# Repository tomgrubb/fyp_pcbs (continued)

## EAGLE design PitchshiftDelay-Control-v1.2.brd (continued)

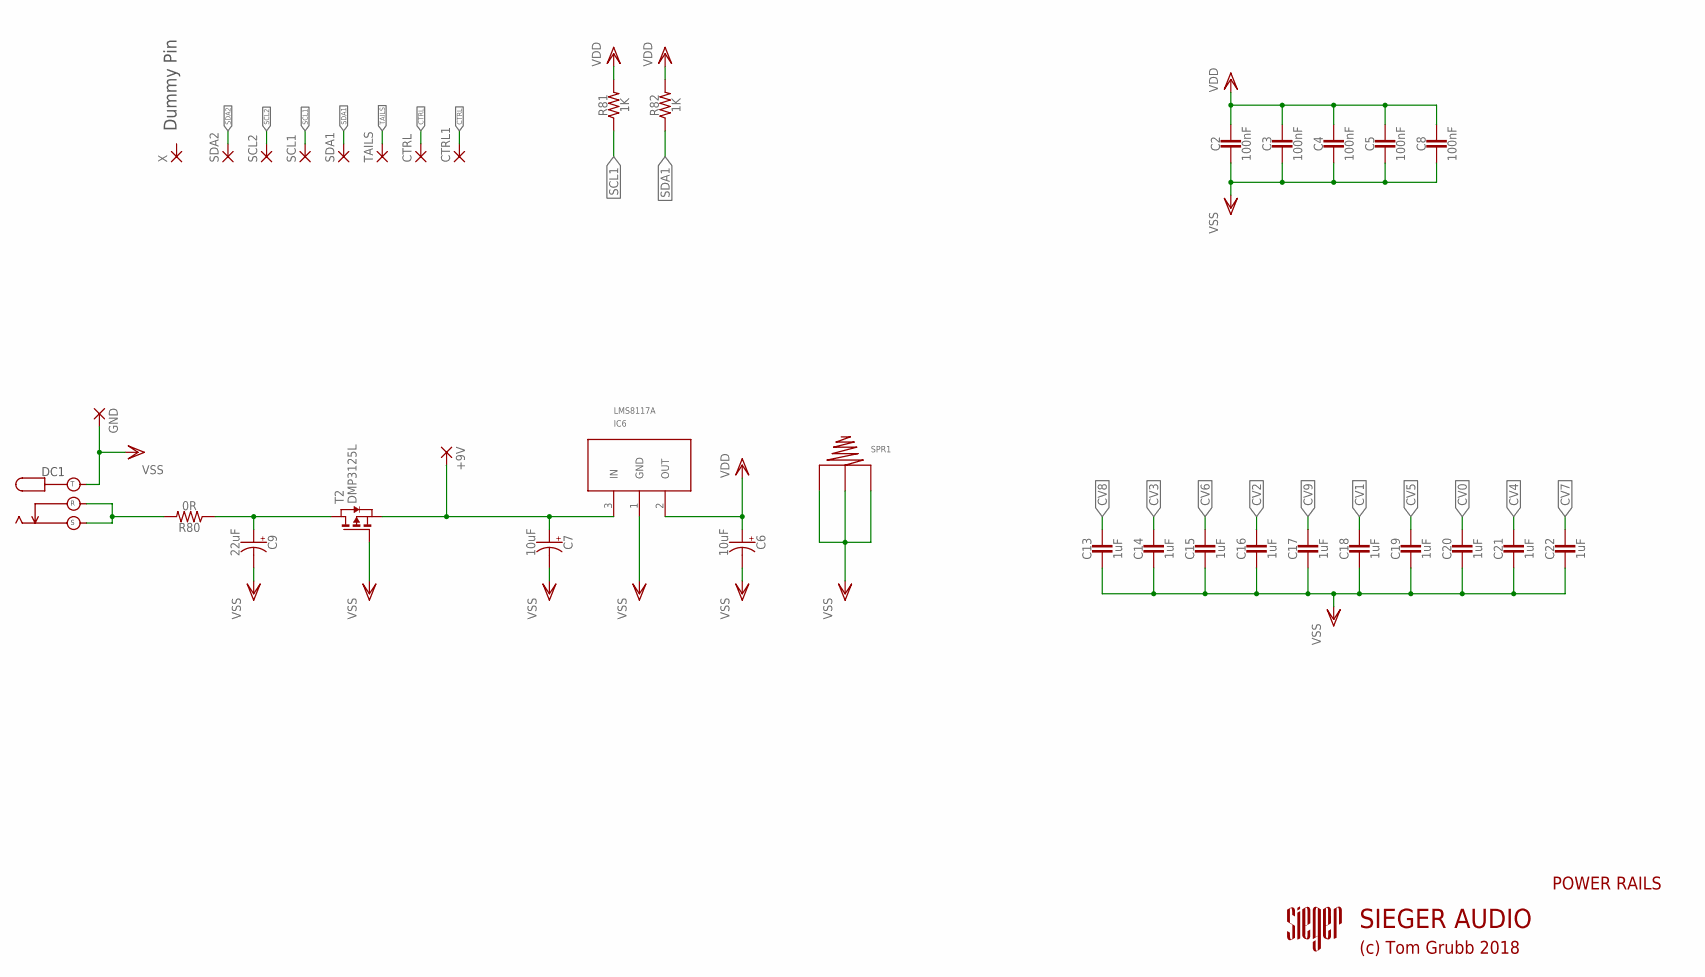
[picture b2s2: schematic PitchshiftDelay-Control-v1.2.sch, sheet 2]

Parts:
+9V: 2,15/1,0
C2, C3, C4, C5, C8: 100nF; 050X030_025
C6, C7: 10uF; 050_020_1
C9: 22uF; 050_020_1
C13, C14, C15, C16, C17, C18, C19, C20, C21, C22: 1uF; 050X030_025
CTRL, CTRL1: 2,15/1,0
DC1: DC_KOBICONN
GND: 2,15/1,0
IC6: LMS8117A; SOT223
R80: 0R; RESISTOR_C0805
R81, R82: 1K; RESISTOR_C0805
SCL1, SCL2: 2,15/1,0
SDA1, SDA2: 2,15/1,0
SPR1: 534-628; 'A'SIZE-PC-SPRING
T2: DMP3125L; SOT-23
TAILS: 2,15/1,0
X: 2,15/1,0

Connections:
9V: +9V.1, C7.+, IC6.3 (IN), T2.2 (S)
CTRL: CTRL.1, CTRL1.1; also elsewhere on the board
CV0: C20.1; also elsewhere on the board
CV1: C18.1; also elsewhere on the board
CV2: C16.1; also elsewhere on the board
CV3: C14.1; also elsewhere on the board
CV4: C21.1; also elsewhere on the board
CV5: C19.1; also elsewhere on the board
CV6: C15.1; also elsewhere on the board
CV7: C22.1; also elsewhere on the board
CV8: C13.1; also elsewhere on the board
CV9: C17.1; also elsewhere on the board
SCL1: R81.1, SCL1.1; also elsewhere on the board
SCL2: SCL2.1; also elsewhere on the board
SDA1: R82.1, SDA1.1; also elsewhere on the board
SDA2: SDA2.1; also elsewhere on the board
TAILS: TAILS.1; also elsewhere on the board
VDD: C2.1, C3.1, C4.1, C5.1, C6.+, C8.1, IC6.2 (OUT), R81.2, R82.2; also elsewhere on the board
VIN: DC1.R, DC1.S, R80.2
VINF: C9.+, R80.1, T2.1 (D)
VSS: C2.2, C3.2, C4.2, C5.2, C6.-, C7.-, C8.2, C9.-, C13.2, C14.2, C15.2, C16.2, C17.2, C18.2, C19.2, C20.2, C21.2, C22.2, DC1.T, GND.1, IC6.1 (GND), SPR1.P$1, SPR1.P$2, SPR1.P$3, T2.3 (G); also elsewhere on the board

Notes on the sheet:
POWER RAILS
Dummy Pin
(c) Tom Grubb 2018
SIEGER AUDIO

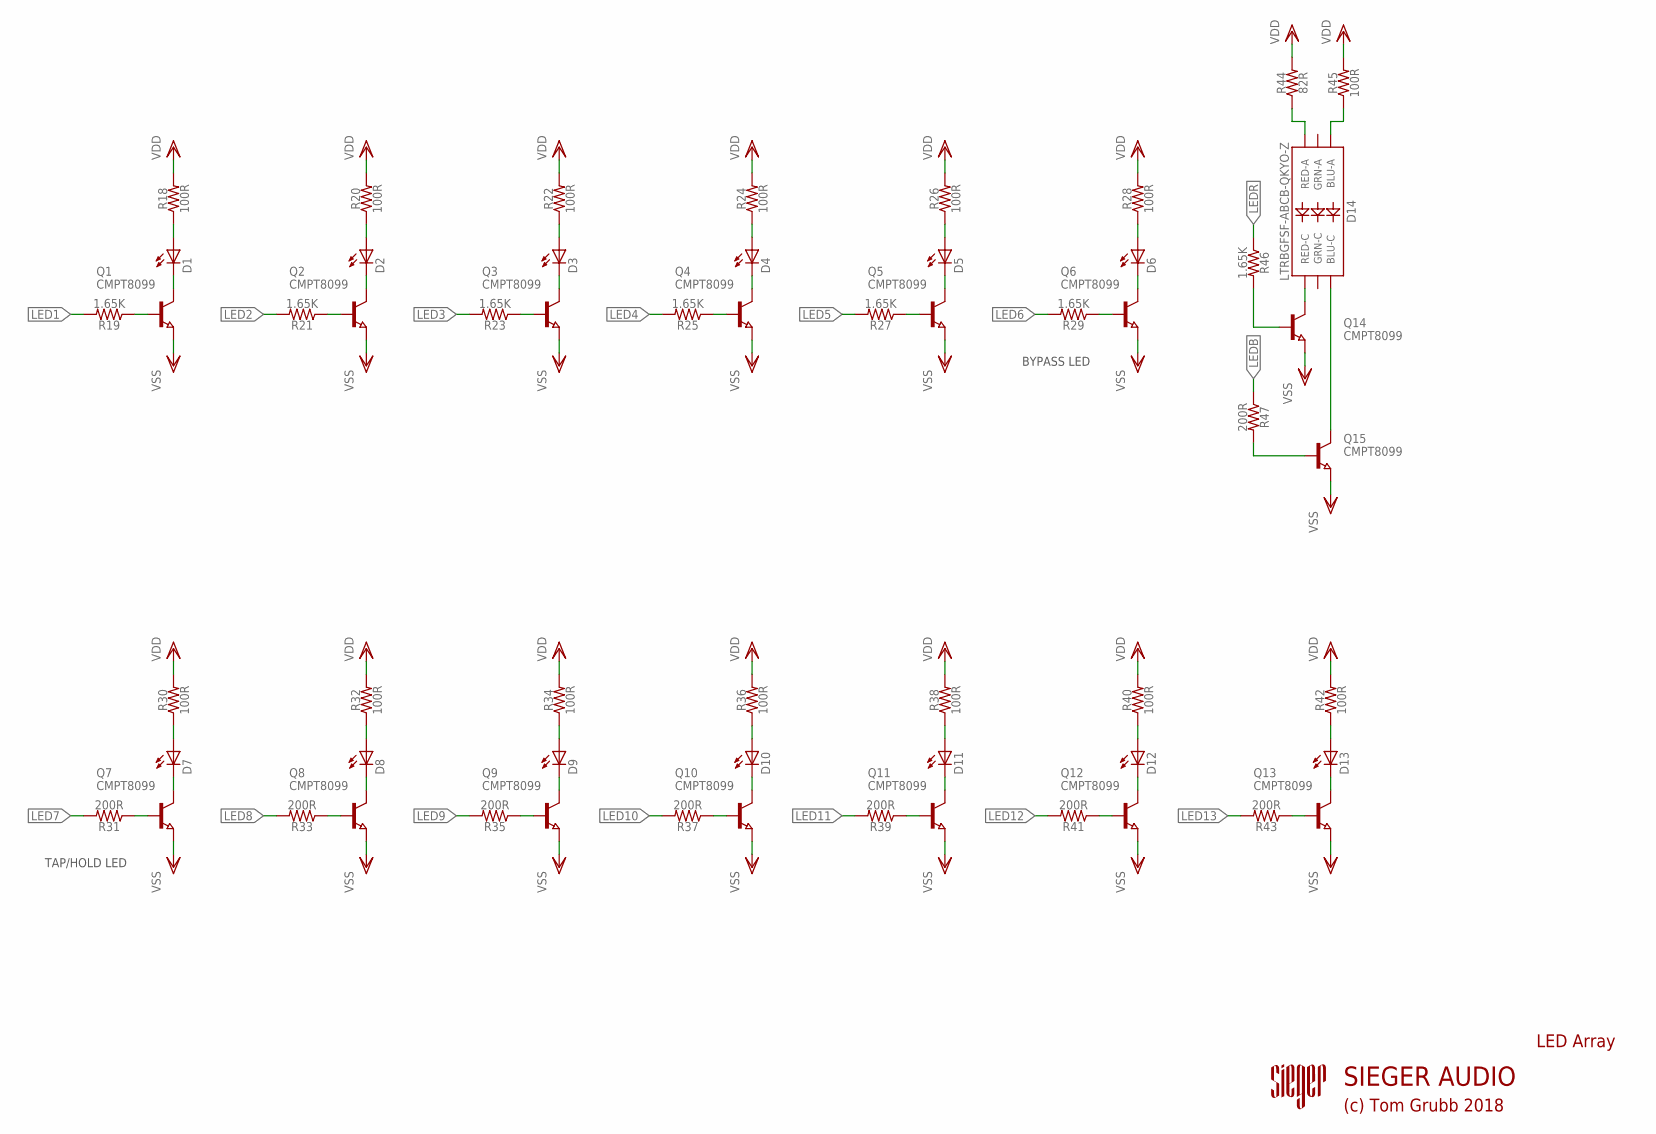
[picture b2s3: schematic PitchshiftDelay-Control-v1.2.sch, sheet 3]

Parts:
D1, D2, D3, D4, D5, D8, D9, D10, D11, D12, D13: LEDCHIP-LED0805; CHIP-LED0805
D6, D7: LEDCHIPLED_1206; CHIPLED_1206
D14: LTRBGFSF-ABCB-QKYO-Z; PLCC-6-LED
Q1, Q2, Q3, Q4, Q5, Q6, Q7, Q8, Q9, Q10, Q11, Q12, Q13, Q14, Q15: CMPT8099; SOT23
R18, R20, R22, R24, R26, R28, R30, R32, R34, R36, R38, R40, R42, R45: 100R; RESISTOR_C0805
R19, R21, R23, R25, R27, R29, R46: 1.65K; RESISTOR_C0805
R31, R33, R35, R37, R39, R41, R43, R47: 200R; RESISTOR_C0805
R44: 82R; RESISTOR_C0805

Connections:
LED1: R19.2; also elsewhere on the board
LED2: R21.2; also elsewhere on the board
LED3: R23.2; also elsewhere on the board
LED4: R25.2; also elsewhere on the board
LED5: R27.2; also elsewhere on the board
LED6: R29.2; also elsewhere on the board
LED7: R31.2; also elsewhere on the board
LED8: R33.2; also elsewhere on the board
LED9: R35.2; also elsewhere on the board
LED10: R37.2; also elsewhere on the board
LED11: R39.2; also elsewhere on the board
LED12: R41.2; also elsewhere on the board
LED13: R43.2; also elsewhere on the board
LEDB: R47.1; also elsewhere on the board
LEDR: R46.1; also elsewhere on the board
unnamed: D1.C, Q1.3 (C)
unnamed: D1.A, R18.1
unnamed: Q2.1 (B), R21.1
unnamed: D2.C, Q2.3 (C)
unnamed: D2.A, R20.1
unnamed: Q1.1 (B), R19.1
unnamed: Q3.1 (B), R23.1
unnamed: D3.C, Q3.3 (C)
unnamed: D3.A, R22.1
unnamed: Q4.1 (B), R25.1
unnamed: D4.C, Q4.3 (C)
unnamed: D4.A, R24.1
unnamed: Q5.1 (B), R27.1
unnamed: D5.C, Q5.3 (C)
unnamed: D5.A, R26.1
unnamed: Q6.1 (B), R29.1
unnamed: D6.C, Q6.3 (C)
unnamed: D6.A, R28.1
unnamed: Q7.1 (B), R31.1
unnamed: D7.C, Q7.3 (C)
unnamed: D7.A, R30.1
unnamed: Q8.1 (B), R33.1
unnamed: D8.C, Q8.3 (C)
unnamed: D8.A, R32.1
unnamed: Q9.1 (B), R35.1
unnamed: D9.C, Q9.3 (C)
unnamed: D9.A, R34.1
unnamed: Q10.1 (B), R37.1
unnamed: D10.C, Q10.3 (C)
unnamed: D10.A, R36.1
unnamed: Q11.1 (B), R39.1
unnamed: D11.C, Q11.3 (C)
unnamed: D11.A, R38.1
unnamed: Q12.1 (B), R41.1
unnamed: D12.C, Q12.3 (C)
unnamed: D12.A, R40.1
unnamed: Q13.1 (B), R43.1
unnamed: D13.C, Q13.3 (C)
unnamed: D13.A, R42.1
unnamed: D14.AR (RED-A), R44.1
unnamed: D14.AB (BLU-A), R45.1
unnamed: D14.CR (RED-C), Q14.3 (C)
unnamed: D14.CB (BLU-C), Q15.3 (C)
unnamed: Q14.1 (B), R46.2
unnamed: Q15.1 (B), R47.2
VDD: R18.2, R20.2, R22.2, R24.2, R26.2, R28.2, R30.2, R32.2, R34.2, R36.2, R38.2, R40.2, R42.2, R44.2, R45.2; also elsewhere on the board
VSS: Q1.2 (E), Q2.2 (E), Q3.2 (E), Q4.2 (E), Q5.2 (E), Q6.2 (E), Q7.2 (E), Q8.2 (E), Q9.2 (E), Q10.2 (E), Q11.2 (E), Q12.2 (E), Q13.2 (E), Q14.2 (E), Q15.2 (E); also elsewhere on the board

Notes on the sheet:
BYPASS LED
TAP/HOLD LED
LED Array
(c) Tom Grubb 2018
SIEGER AUDIO

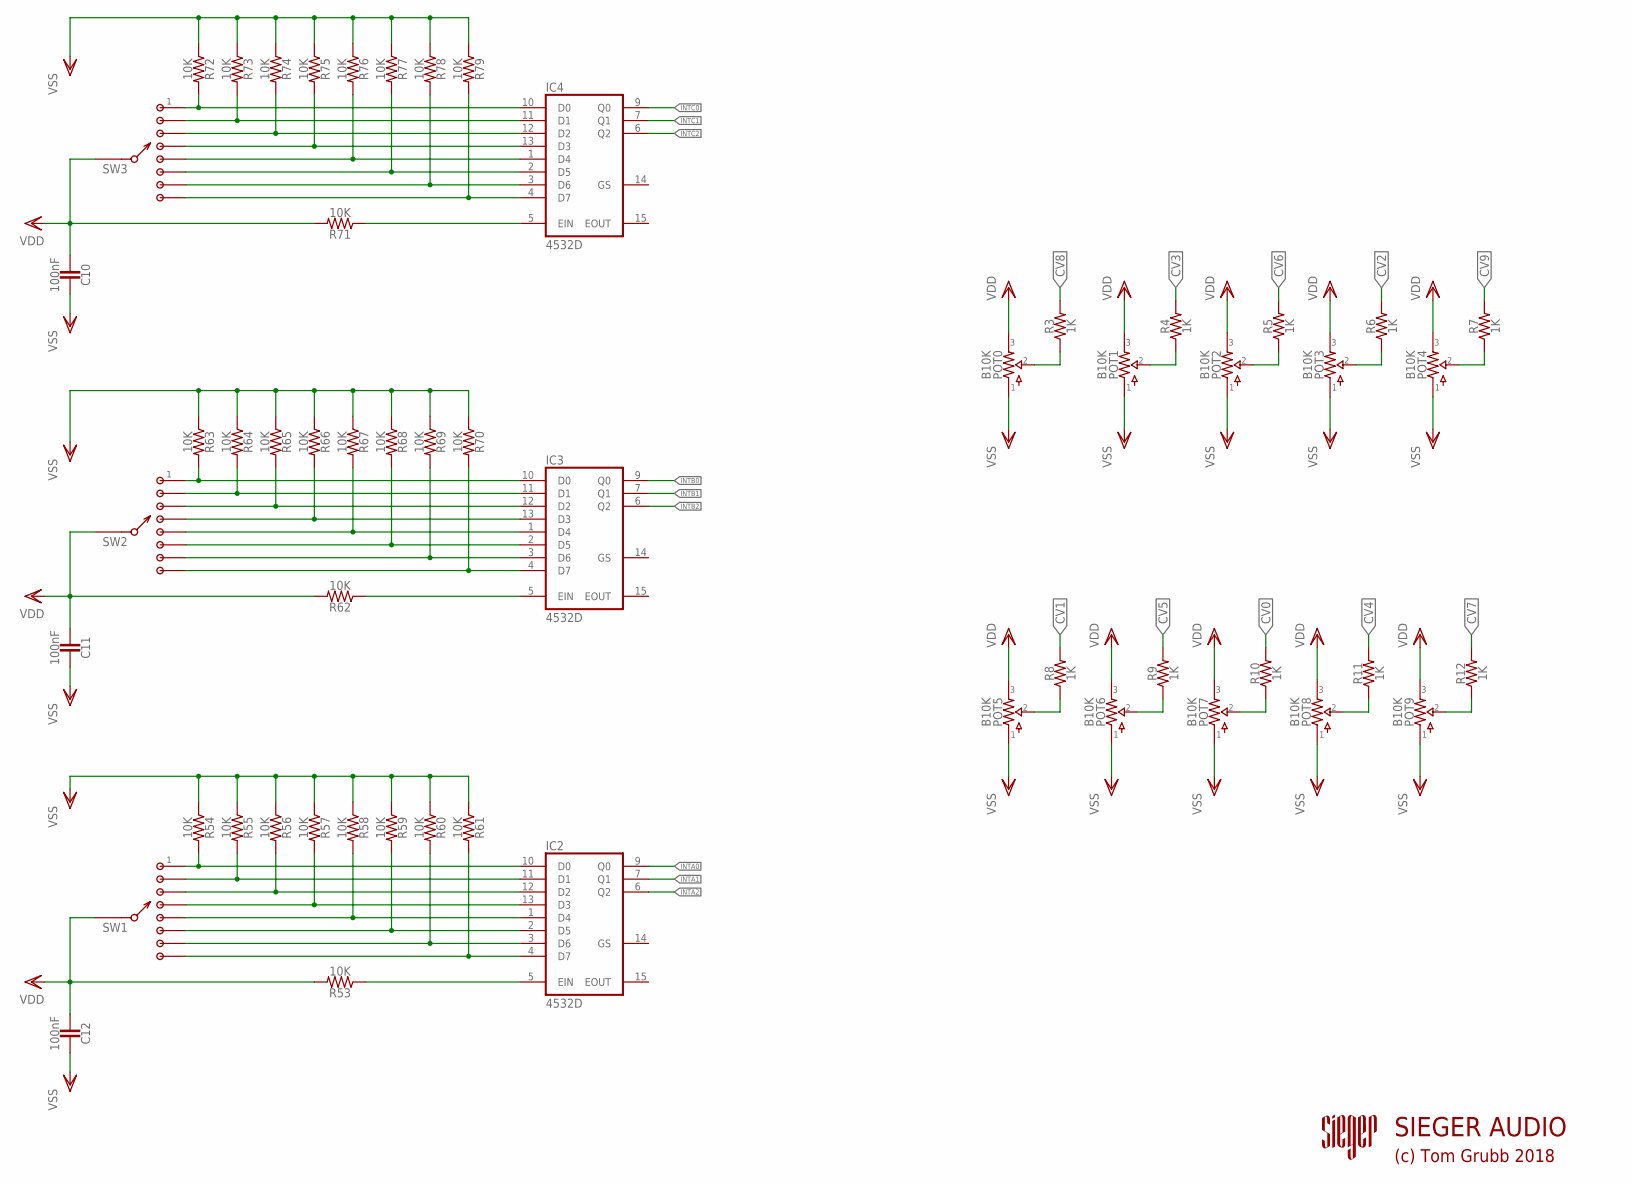
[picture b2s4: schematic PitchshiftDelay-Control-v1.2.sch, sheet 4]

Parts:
C10, C11, C12: 100nF; 050X030_025
IC2, IC3, IC4: 4532D; SO16
POT0, POT1, POT2, POT3, POT4, POT5, POT6, POT7, POT8, POT9: B10K; 9MM_W/MOUNTS-2MMHOLES
R3, R4, R5, R6, R7, R8, R9, R10, R11, R12: 1K; RESISTOR_C0805
R53, R54, R55, R56, R57, R58, R59, R60, R61, R62, R63, R64, R65, R66, R67, R68, R69, R70, R71, R72, R73, R74, R75, R76, R77, R78, R79: 10K; RESISTOR_C0805
SW1, SW2, SW3: 1P8T; SMALLROTARY

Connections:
CV0: R10.2; also elsewhere on the board
CV1: R8.2; also elsewhere on the board
CV2: R6.2; also elsewhere on the board
CV3: R4.2; also elsewhere on the board
CV4: R11.2; also elsewhere on the board
CV5: R9.2; also elsewhere on the board
CV6: R5.2; also elsewhere on the board
CV7: R12.2; also elsewhere on the board
CV8: R3.2; also elsewhere on the board
CV9: R7.2; also elsewhere on the board
INTA0: IC2.9 (Q0); also elsewhere on the board
INTA1: IC2.7 (Q1); also elsewhere on the board
INTA2: IC2.6 (Q2); also elsewhere on the board
INTB0: IC3.9 (Q0); also elsewhere on the board
INTB1: IC3.7 (Q1); also elsewhere on the board
INTB2: IC3.6 (Q2); also elsewhere on the board
INTC0: IC4.9 (Q0); also elsewhere on the board
INTC1: IC4.7 (Q1); also elsewhere on the board
INTC2: IC4.6 (Q2); also elsewhere on the board
unnamed: POT0.P$2 (2), R3.1
unnamed: POT1.P$2 (2), R4.1
unnamed: POT2.P$2 (2), R5.1
unnamed: POT3.P$2 (2), R6.1
unnamed: POT4.P$2 (2), R7.1
unnamed: POT5.P$2 (2), R8.1
unnamed: POT6.P$2 (2), R9.1
unnamed: POT7.P$2 (2), R10.1
unnamed: POT8.P$2 (2), R11.1
unnamed: POT9.P$2 (2), R12.1
unnamed: IC2.5 (EIN), R53.1
unnamed: IC3.10 (D0), R63.2, SW2.1
unnamed: IC3.11 (D1), R64.2, SW2.2
unnamed: IC3.12 (D2), R65.2, SW2.3
unnamed: IC3.13 (D3), R66.2, SW2.4
unnamed: IC2.10 (D0), R54.2, SW1.1
unnamed: IC2.11 (D1), R55.2, SW1.2
unnamed: IC2.12 (D2), R56.2, SW1.3
unnamed: IC2.13 (D3), R57.2, SW1.4
unnamed: IC2.1 (D4), R58.2, SW1.5
unnamed: IC2.2 (D5), R59.2, SW1.6
unnamed: IC2.3 (D6), R60.2, SW1.7
unnamed: IC2.4 (D7), R61.2, SW1.8
unnamed: IC3.1 (D4), R67.2, SW2.5
unnamed: IC3.2 (D5), R68.2, SW2.6
unnamed: IC3.3 (D6), R69.2, SW2.7
unnamed: IC3.4 (D7), R70.2, SW2.8
unnamed: IC3.5 (EIN), R62.1
unnamed: IC4.10 (D0), R72.2, SW3.1
unnamed: IC4.11 (D1), R73.2, SW3.2
unnamed: IC4.12 (D2), R74.2, SW3.3
unnamed: IC4.13 (D3), R75.2, SW3.4
unnamed: IC4.1 (D4), R76.2, SW3.5
unnamed: IC4.2 (D5), R77.2, SW3.6
unnamed: IC4.3 (D6), R78.2, SW3.7
unnamed: IC4.4 (D7), R79.2, SW3.8
unnamed: IC4.5 (EIN), R71.1
VDD: C10.2, C11.2, C12.2, IC2.16 (VDD), IC3.16 (VDD), IC4.16 (VDD), POT0.P$3 (3), POT1.P$3 (3), POT2.P$3 (3), POT3.P$3 (3), POT4.P$3 (3), POT5.P$3 (3), POT6.P$3 (3), POT7.P$3 (3), POT8.P$3 (3), POT9.P$3 (3), R53.2, R62.2, R71.2, SW1.C (A), SW2.C (A), SW3.C (A); also elsewhere on the board
VSS: C10.1, C11.1, C12.1, IC2.8 (VSS), IC3.8 (VSS), IC4.8 (VSS), POT0.P$1 (1), POT1.P$1 (1), POT2.P$1 (1), POT3.P$1 (1), POT4.P$1 (1), POT5.P$1 (1), POT6.P$1 (1), POT7.P$1 (1), POT8.P$1 (1), POT9.P$1 (1), R54.1, R55.1, R56.1, R57.1, R58.1, R59.1, R60.1, R61.1, R63.1, R64.1, R65.1, R66.1, R67.1, R68.1, R69.1, R70.1, R72.1, R73.1, R74.1, R75.1, R76.1, R77.1, R78.1, R79.1; also elsewhere on the board

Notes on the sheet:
(c) Tom Grubb 2018
SIEGER AUDIO

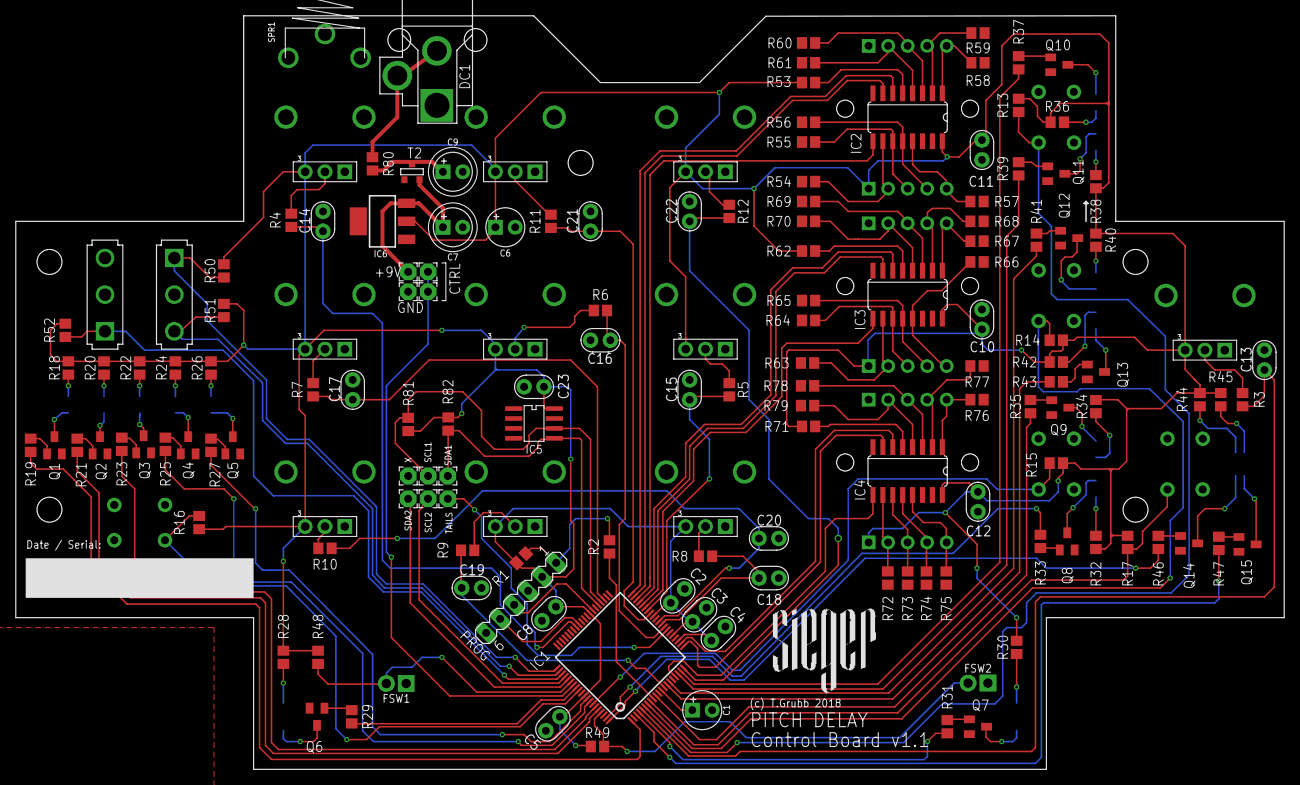
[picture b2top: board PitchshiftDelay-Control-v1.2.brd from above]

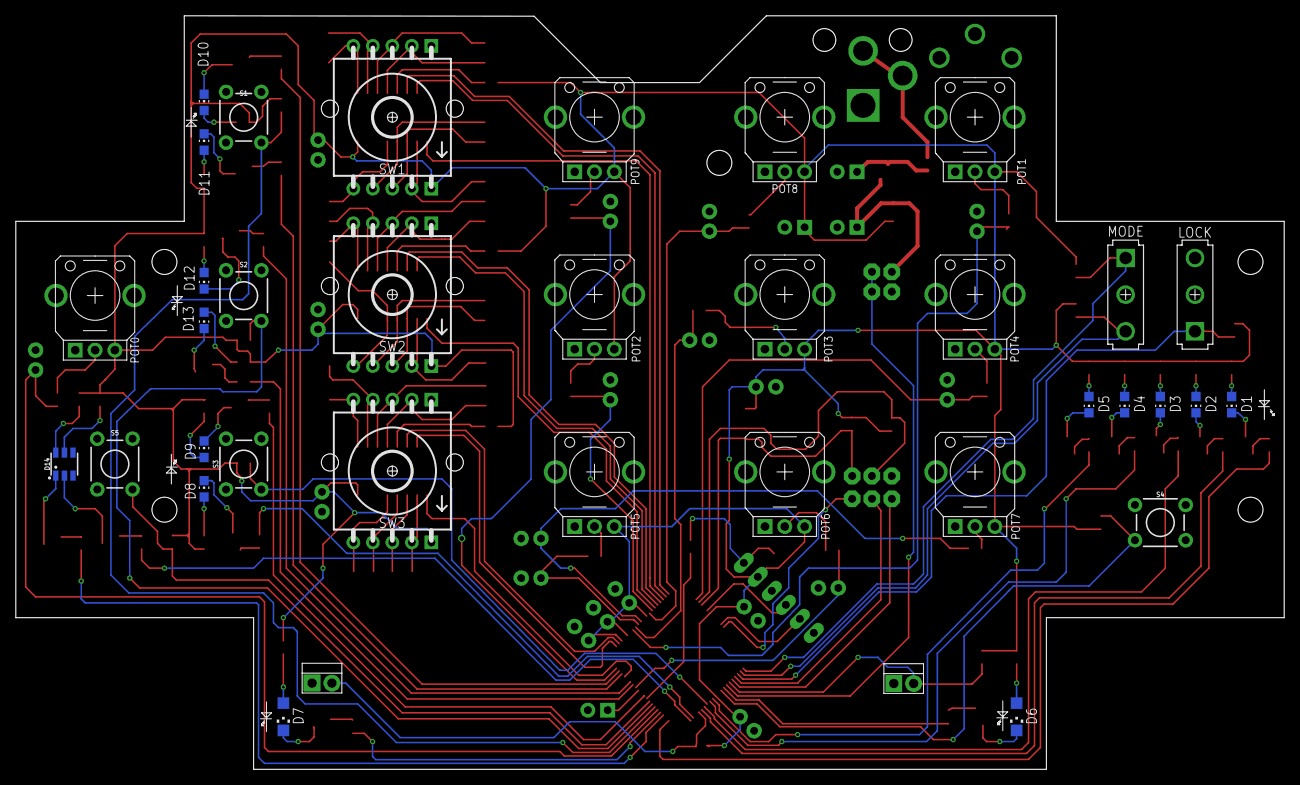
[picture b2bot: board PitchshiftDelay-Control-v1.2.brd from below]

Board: 2 copper layers, 162.6 x 96.6 mm, 177 parts (21 on the bottom side), 142 nets.

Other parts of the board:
U$1: LARGE
